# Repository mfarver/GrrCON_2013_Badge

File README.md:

GrrCON_2013_Badge
=================

Schematics, Board Designs and code for GrrCON 2013 Badges.

Schematic and Board layouts require Eagle 6.4.

Badge is based on Arduino Uno Rev 3.  http://arduino.cc

The board layout and schematic are released under the Creative Commons Share Alike license.  The GrrCON "skull" outline of the board should not be used without permission.

When programming the bootloader on the Main ATMEGA328P processor fuses are:
efuse:0x06 hfuse:0xD6 lfuse:0x7F

Custom bootloader and board definition in the hardware directory.

https://github.com/arduino/Arduino/blob/master/hardware/arduino/firmwares/atmegaxxu2/Arduino-COMBINED-dfu-usbserial-atmega16u2-Uno-Rev3.hex
lfuse:w:0xFF:m hfuse:w:0xD9:m efuse:w:0xF4:m lock:w:0x0F:m

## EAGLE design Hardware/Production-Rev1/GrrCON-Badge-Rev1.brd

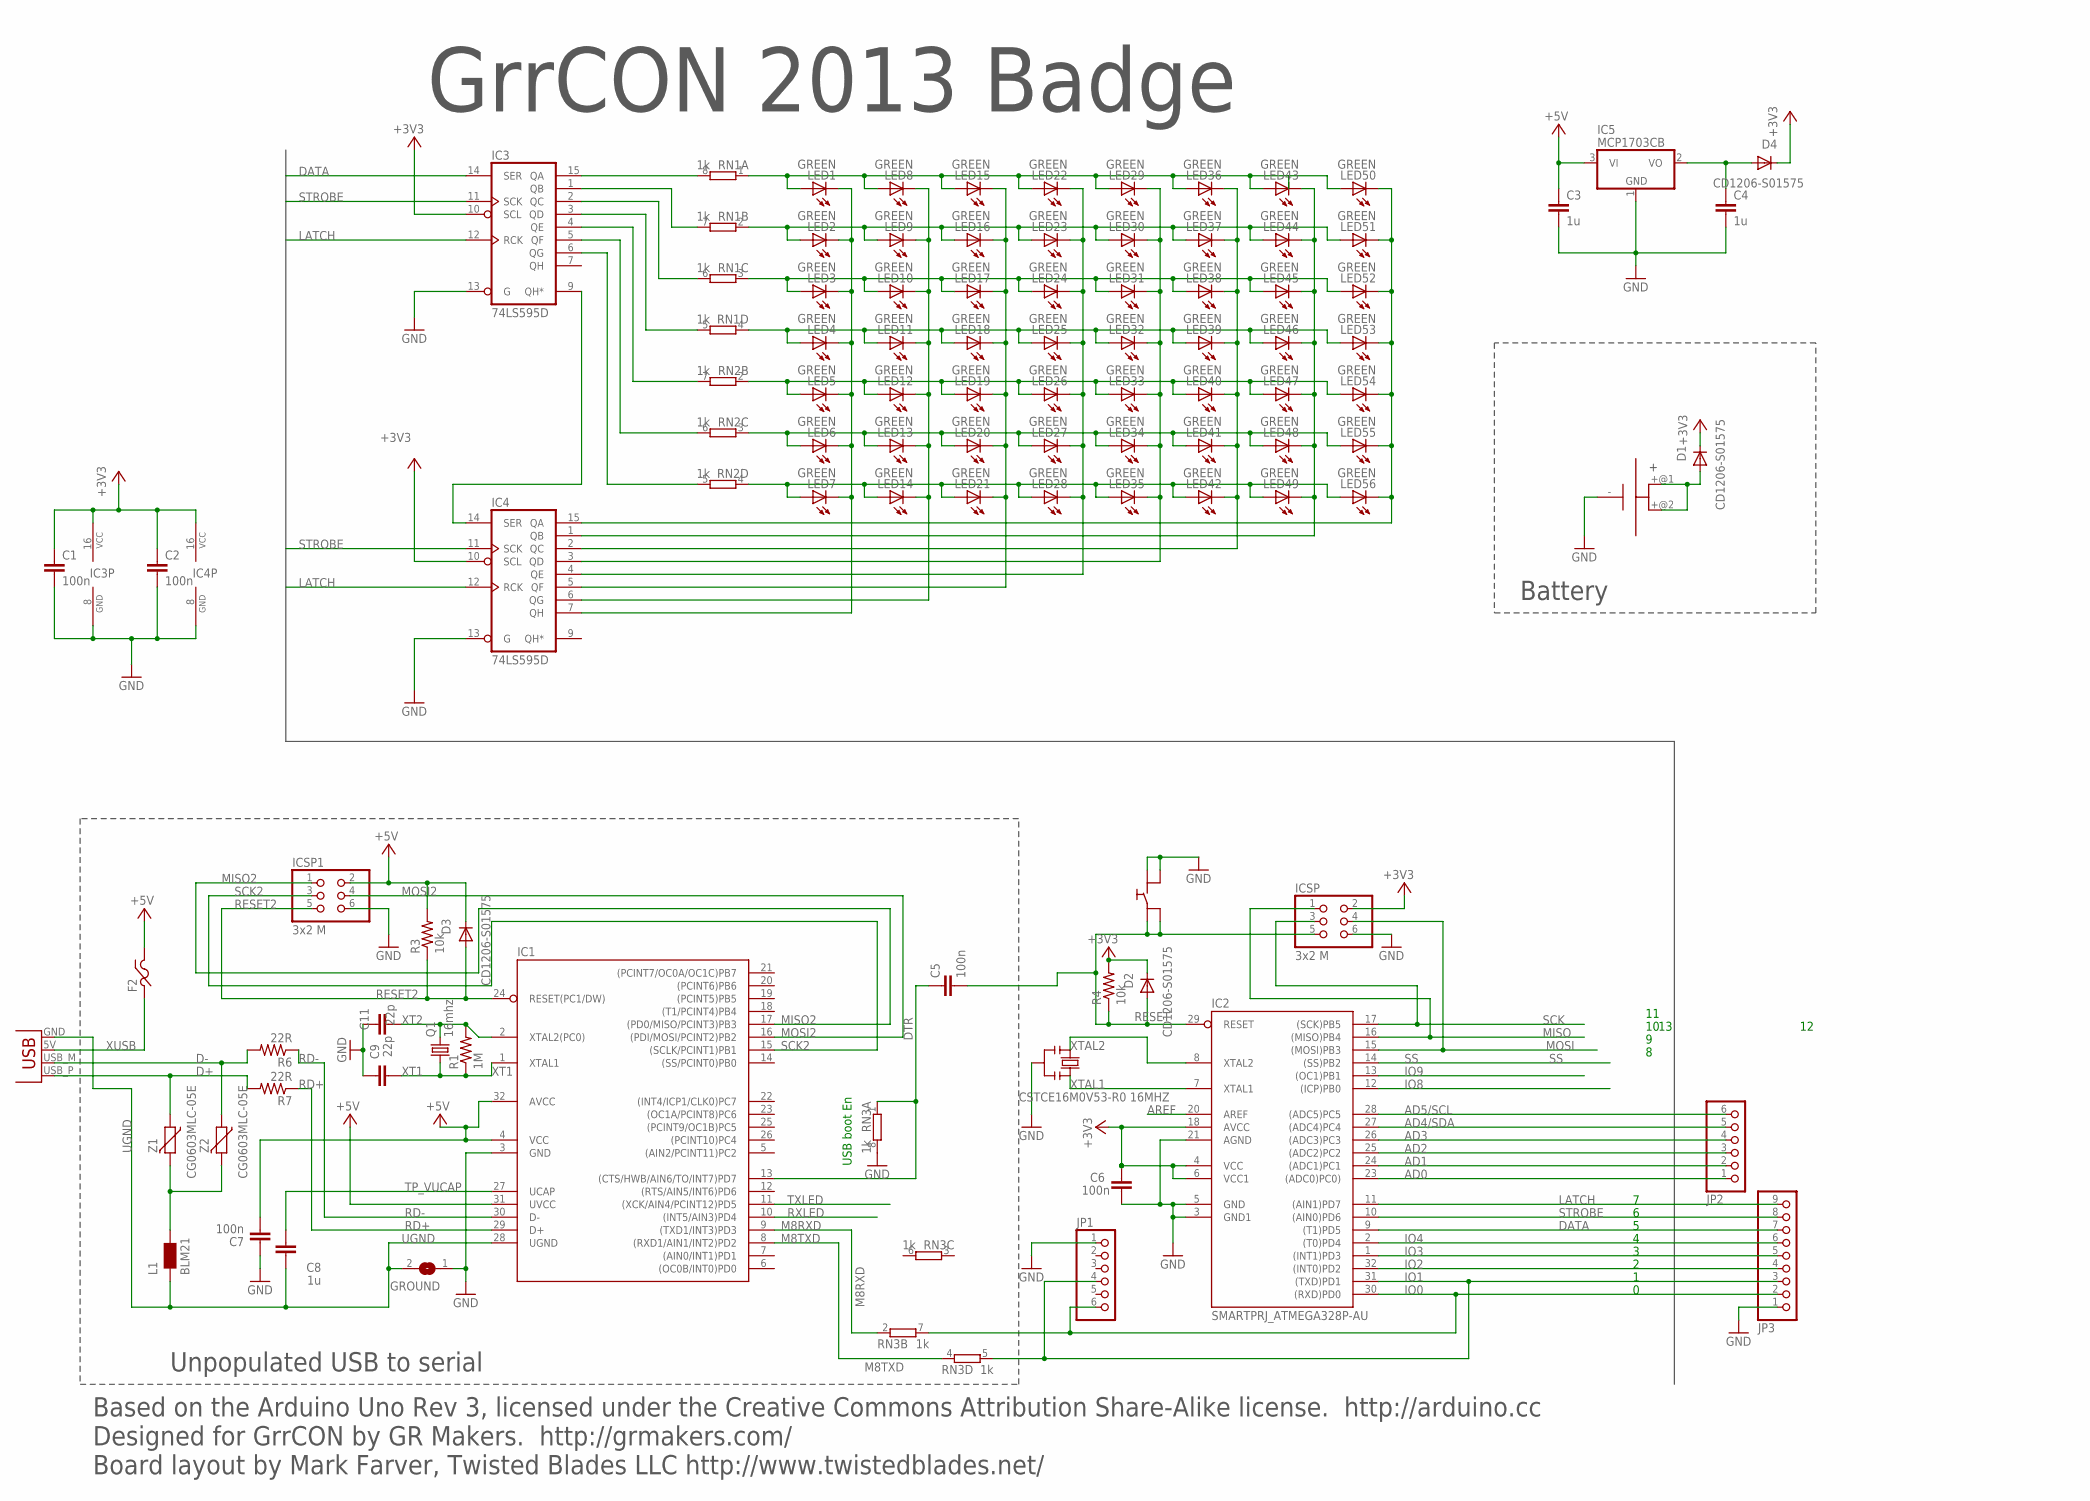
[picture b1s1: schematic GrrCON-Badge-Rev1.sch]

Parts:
B1: KEYSTONE_COIN2450; 3009
C1, C2, C5, C6, C7: 100n; C0805
C3, C4, C8: 1u; C0805
C9, C11: 22p; C0805
D1, D2, D3, D4: CD1206-S01575; MINIMELF
F2: PTC-FUSE-US1206; F1206
GROUND: SJ
IC1: ATMEGA16U2AU; SMARTPRJ_TQFP32-08
IC2: SMARTPRJ_ATMEGA328P-AU; SMARTPRJ_TQFP32-08
IC3, IC4: 74LS595D; SO16
IC5: MCP1703CB; SOT23
ICSP, ICSP1: 3x2 M; 2X03
JP1, JP2: PINHD-1X6; 1X06
JP3: PINHD-1X9; 1X09
L1: BLM21; 0805
LED1, LED2, LED3, LED4, LED5, LED6, LED7, LED8, LED9, LED10, LED11, LED12, LED13, LED14, LED15, LED16, LED17, LED18, LED19, LED20, LED21, LED22, LED23, LED24, LED25, LED26, LED27, LED28, LED29, LED30, LED31, LED32, LED33, LED34, LED35, LED36, LED37, LED38, LED39, LED40, LED41, LED42, LED43, LED44, LED45, LED46, LED47, LED48, LED49, LED50, LED51, LED52, LED53, LED54, LED55, LED56: GREEN; CHIPLED_0603
Q1: 16mhz; SM49
R1: 1M; R0805
R3, R4: 10k; R0805
R6, R7: 22R; R0805
RN1, RN2, RN3: 1k; RESISTOR-DIL_CAY16
SW1: PTS645SMT
X1: USBPCB; USB-A-PCB
Y2: CSTCE16M0V53-R0 16MHZ; RESONATOR
Z1, Z2: CG0603MLC-05E; CT/CN0603

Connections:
+3V3: C1.1, C2.1, C6.2, D1.C, D2.C, D4.C, IC2.4 (VCC), IC2.6 (VCC1), IC2.18 (AVCC), IC3.10 (SCL), IC3.16 (VCC), IC4.10 (SCL), IC4.16 (VCC), ICSP.2, R4.2
+5V: C3.1, C7.1, D3.C, F2.2, IC1.4 (VCC), IC1.31 (UVCC), IC1.32 (AVCC), IC5.3 (VI), ICSP1.2, R3.2
AD0: IC2.23 ((ADC0)PC0)), JP2.1
AD1: IC2.24 ((ADC1)PC1), JP2.2
AD2: IC2.25 ((ADC2)PC2), JP2.3
AD3: IC2.26 ((ADC3)PC3), JP2.4
AD4/SDA: IC2.27 ((ADC4)PC4), JP2.5
AD5/SCL: IC2.28 ((ADC5)PC5), JP2.6
AREF: IC2.20 (AREF)
D+: R7.2, X1.USB_P (D+), Z1.1
D-: R6.2, X1.USB_M (D-), Z2.1
DATA: IC2.9 ((T1)PD5), IC3.14 (SER), JP3.7
DTR: C5.1, IC1.13 ((CTS/HWB/AIN6/TO/INT7)PD7), RN3.1
GND: B1.-, C1.2, C2.2, C3.2, C4.2, C6.1, C7.2, C9.2, C11.2, GROUND.1, IC1.3 (GND), IC2.3 (GND1), IC2.5 (GND), IC2.21 (AGND), IC3.8 (GND), IC3.13 (G), IC4.8 (GND), IC4.13 (G), IC5.1 (GND), ICSP.6, ICSP1.6, JP1.1, JP3.1, RN3.8 (2), SW1.2A, SW1.2B, Y2.2
IO0: IC2.30 ((RXD)PD0), JP1.6, JP3.2, RN3.7 (2)
IO1: IC2.31 ((TXD)PD1), JP1.4, JP3.3, RN3.5 (2)
IO2: IC2.32 ((INT0)PD2), JP3.4
IO3: IC2.1 ((INT1)PD3), JP3.5
IO4: IC2.2 ((T0)PD4), JP3.6
IO8: IC2.12 ((ICP)PB0)
IO9: IC2.13 ((OC1)PB1)
LATCH: IC2.11 ((AIN1)PD7), IC3.12 (RCK), IC4.12 (RCK), JP3.9
M8RXD: IC1.9 ((TXD1/INT3)PD3), RN3.2 (1)
M8TXD: IC1.8 ((RXD1/AIN1/INT2)PD2), RN3.4 (1)
MISO: IC2.16 ((MISO)PB4), ICSP.1
MISO2: IC1.17 ((PD0/MISO/PCINT3)PB3), ICSP1.1
MOSI: IC2.15 ((MOSI)PB3), ICSP.4
MOSI2: IC1.16 ((PDI/MOSI/PCINT2)PB2), ICSP1.4
unnamed: IC4.7 (QH), LED1.C, LED2.C, LED3.C, LED4.C, LED5.C, LED6.C, LED7.C
unnamed: LED2.A, LED9.A, LED16.A, LED23.A, LED30.A, LED37.A, LED44.A, LED51.A, RN1.2 (1)
unnamed: IC3.6 (QG), RN2.5 (2)
unnamed: LED3.A, LED10.A, LED17.A, LED24.A, LED31.A, LED38.A, LED45.A, LED52.A, RN1.3 (1)
unnamed: LED4.A, LED11.A, LED18.A, LED25.A, LED32.A, LED39.A, LED46.A, LED53.A, RN1.4 (1)
unnamed: IC3.9 (QH*), IC4.14 (SER)
unnamed: IC3.5 (QF), RN2.6 (2)
unnamed: IC3.4 (QE), RN2.7 (2)
unnamed: IC3.3 (QD), RN1.5 (2)
unnamed: IC4.6 (QG), LED8.C, LED9.C, LED10.C, LED11.C, LED12.C, LED13.C, LED14.C
unnamed: IC3.2 (QC), RN1.6 (2)
unnamed: IC3.1 (QB), RN1.7 (2)
unnamed: IC3.15 (QA), RN1.8 (2)
unnamed: B1.+@1 (+), B1.+@2 (+), D1.A
unnamed: C4.1, D4.A, IC5.2 (VO)
unnamed: IC4.5 (QF), LED15.C, LED16.C, LED17.C, LED18.C, LED19.C, LED20.C, LED21.C
unnamed: IC4.4 (QE), LED22.C, LED23.C, LED24.C, LED25.C, LED26.C, LED27.C, LED28.C
unnamed: IC4.3 (QD), LED29.C, LED30.C, LED31.C, LED32.C, LED33.C, LED34.C, LED35.C
unnamed: IC4.2 (QC), LED36.C, LED37.C, LED38.C, LED39.C, LED40.C, LED41.C, LED42.C
unnamed: IC4.1 (QB), LED43.C, LED44.C, LED45.C, LED46.C, LED47.C, LED48.C, LED49.C
unnamed: IC4.15 (QA), LED50.C, LED51.C, LED52.C, LED53.C, LED54.C, LED55.C, LED56.C
unnamed: LED5.A, LED12.A, LED19.A, LED26.A, LED33.A, LED40.A, LED47.A, LED54.A, RN2.2 (1)
unnamed: LED6.A, LED13.A, LED20.A, LED27.A, LED34.A, LED41.A, LED48.A, LED55.A, RN2.3 (1)
unnamed: LED7.A, LED14.A, LED21.A, LED28.A, LED35.A, LED42.A, LED49.A, LED56.A, RN2.4 (1)
unnamed: LED1.A, LED8.A, LED15.A, LED22.A, LED29.A, LED36.A, LED43.A, LED50.A, RN1.1
RD+: IC1.29 (D+), R7.1
RD-: IC1.30 (D-), R6.1
RESET: C5.2, D2.A, IC2.29 (RESET), ICSP.5, R4.1, SW1.1A, SW1.1B
RESET2: D3.A, IC1.24 (RESET(PC1/DW)), ICSP1.5, R3.1
RXLED: IC1.10 ((INT5/AIN3)PD4)
SCK: IC2.17 ((SCK)PB5), ICSP.3
SCK2: IC1.15 ((SCLK/PCINT1)PB1), ICSP1.3
SS: IC2.14 ((SS)PB2)
STROBE: IC2.10 ((AIN0)PD6), IC3.11 (SCK), IC4.11 (SCK), JP3.8
TP_VUCAP: C8.1, IC1.27 (UCAP)
TXLED: IC1.11 ((XCK/AIN4/PCINT12)PD5)
UGND: C8.2, GROUND.2, IC1.28 (UGND), L1.1, X1.GND
USHIELD: L1.2, Z1.2, Z2.2
XT1: C9.1, IC1.1 (XTAL1), Q1.1, R1.1
XT2: C11.1, IC1.2 (XTAL2(PC0)), Q1.2, R1.2
XTAL1: IC2.7 (XTAL1), Y2.3
XTAL2: IC2.8 (XTAL2), Y2.1
XUSB: F2.1, X1.5V (VBUS)

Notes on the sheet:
USB boot En
Unpopulated USB to serial
Battery
GrrCON 2013 Badge
Based on the Arduino Uno Rev 3, licensed under the Creative Commons Attribution Share-Alike license. http://arduino.cc Designed for GrrCON by GR Makers. http://grmakers.com/ Board layout by Mark Farver, Twisted Blades LLC http://www.twistedblades.net/

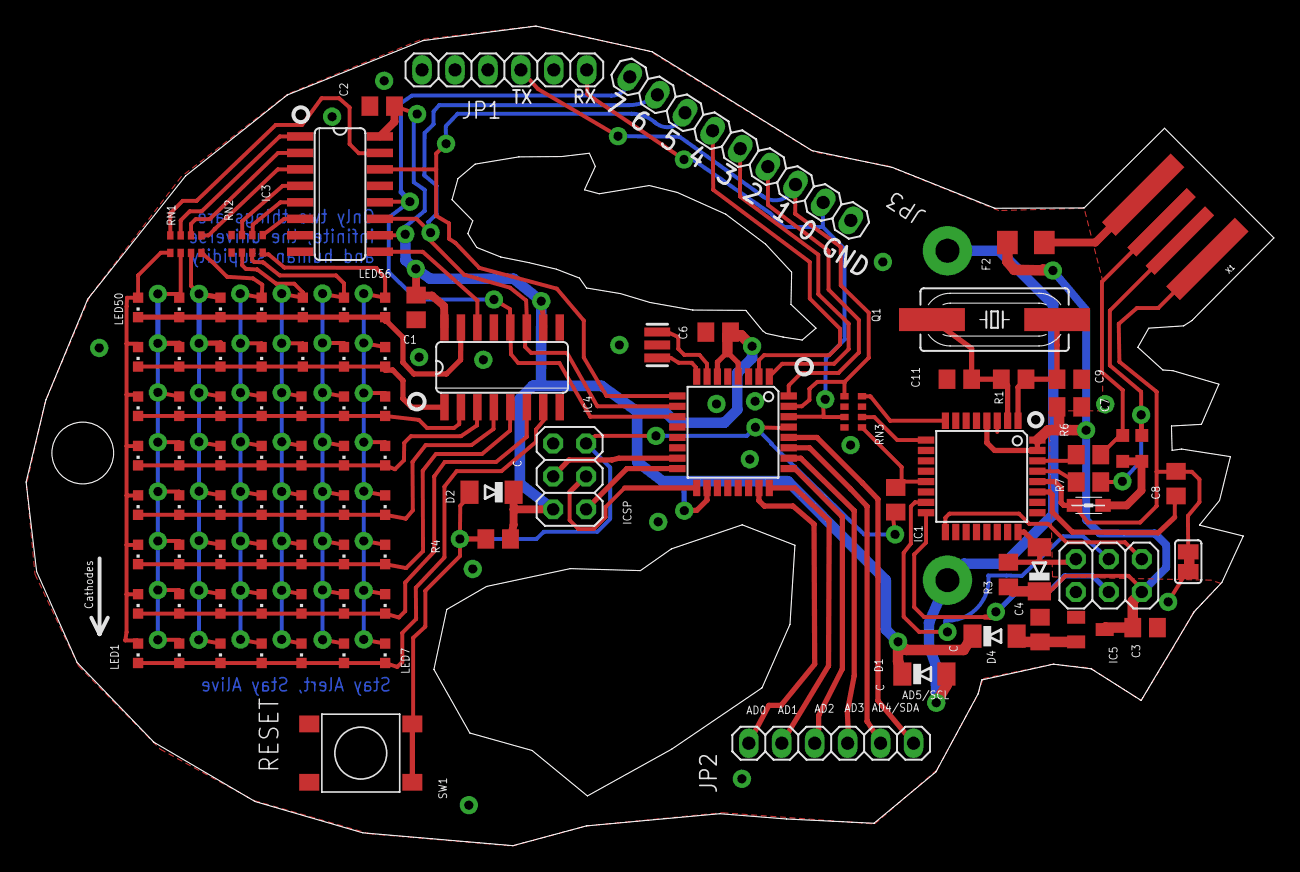
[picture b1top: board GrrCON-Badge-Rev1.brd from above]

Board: 2 copper layers, 96.2 x 63.2 mm, 98 parts (1 on the bottom side), 65 nets.

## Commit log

2013-08-27 Initial load of production and prototype eagle files and code
2013-08-28 Added license header, and fixed overrun
    Fixed issue where last character would read columns from beyond end of
    message array.. now correctly wraps back to the beginning.
2013-08-31 Added 1/8 clock prescaler
    Slowed clock down to improve low voltage performance on cheap batteries.
2013-09-02 Fixed flicker at 2 mhz clock
    Swapped digitalWrite functions for direct port access. Significant
    speed up eliminated flicker
2013-09-02 Added custom 2mhz/19200 bootloader
    Added patch to optiboot source to compile a custom bootloader that runs
    at 2mhz. The fuses are now setup to divide the 16mhz external clock by
    8 and brown out detect at 1.8V. This should run at a more battery
    friendly 2mhz down to 1.8V.
2013-09-02 Changed to EEPROM and serial updating.
    Completely untested, but it has everything I can think of.
2013-09-02 Fixed missing Power Net, spelling
    Fixed Spelling of Arduino on silk and documentation. Fixed missing
    power net to ATMEGA328P processor
2013-09-02 Save message to EEPROM fixes
    Changed the message storage in EEPROM to a Pascal string with the length
    at the start. This allows persistence thru resets/battery changes.
2013-09-02 fix serial noise corrupting message
    Added a write buffer so serial noise when USB is disconnected does not
    trash message. Also three CRs in a row are required to commit message
2013-09-02 Restart scroll on update and spit out the length when asked.
2013-09-02 Added tool to update message.
2013-09-08 Add skull glyph and highest character value const
    Add a constant containing the highest character defined in our font,
    and add a skull glyph at value 127 (DEL) for fun.
2013-09-08 Cache message in RAM. Protect against overrun.
    Load the message into RAM on startup. Use the same load routine after
    a new message is defined in the serial handler.
    Add a stub for a future demo routine, which will be called if either
    the message length is zero, or it is 255 (which is what EEPROM is set
    to when erased).
    In order to detect uninitialized EEPROM, our max message length is
2013-09-08 put local loop var inside for delcaration
2013-09-08 global var cleanup. misc fixes.
2013-09-08 implement some demo functions
2013-09-08 add ctrl-c handler to serialEvent
2013-09-08 fix demo loop off-by-one
2013-09-08 fix small mistake in demo loop
2013-09-08 add alternating lines demo mode. slow all demos.
2013-09-08 ifdef out serial code. seems to flake out very easilly
2013-09-08 update tool to match serial code
2013-09-09 reduce scroll refresh count expecting clock reduction
2013-09-10 re-enable serial code
    You know... it helps to use the correct board profile when compiling
    the serial code.
2013-09-10 add default messages for different badge types
    read the last byte of eeprom to get the badge type and then use it to
    look up a default message for that type of badge, if no message is
    defined.
    Also, only show the demo loop on startup if there is a message or
    badge type defined. Otherwise, show the demo loop endlessly.
2013-09-10 verify loaded message matches stored CRC
2013-09-10 replace pixel demo with single-row demo
2013-09-10 store crc big-endian
2013-09-10 update serial programming protocol
    update serial programming protocol to be more resistant to noise from
    handling.
    To update, send 9 garbage characters to make certain you are in the base
    mode. space or newline work well for this.
    Then:
    To update the message:
2013-09-10 fix code to match last commit comment
    in the previous commit, I said the badge type was sent in ascii and
    that the badge type change attention sequence was 0x01. I forgot to
    make the changes to the code to match.
2013-09-10 add tools to program badges in batches
2013-09-10 missed in previous commit of this file
2013-09-10 allow programmer to be specified in environment
2013-09-10 forgot to add n to badge type check
2013-09-10 a version of doboard that only loads the avr
2013-09-10 add python util to set badge type
2013-09-10 give message that we're done sending
2013-09-11 add pseudocode of the programming protocol
2013-09-11 Updated BOM
    Updated BOM spreadsheet and added additional comments.
2013-09-11 add tool to set badge message string
2013-09-11 wait for the badge to be ready after open
2013-09-12 fix bug with zero-length string
    The zero-length string would be the way to set the badges back to displaying
    the default message. However, there was a problem with sending a zero-length
    string, where it would need 256 additional bytes before it wrapped around and
    did as intended.
2013-09-12 and commit the code for that last commit
2013-09-12 add tool to automate reload of code
2013-09-12 Combined load_string and setbadge w/ OS checks
    This file now checks for Linux or OSX, then asks which action you'd
    like to take. Each action has sub-options in order to work with the
    board.
2013-09-12 no serial port should be an error on all platforms
    Also, when exit is selected, give a different exit code, so we can
    use it in a loop.
2013-09-16 add PDF of schematic

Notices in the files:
Hardware/Prototypes/GrrCON-Badge-Rev1.sch:
Based on the Ardunio Uno Rev 3, licensed under the Creative Commons Attribution Share-Alike license.  http://arduino.cc
